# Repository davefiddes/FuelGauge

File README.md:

# Linear Fuel Gauge

This project allows an accurate linear fuel readout to be created for vehicles with unusually shaped fuel tanks and/or mismatched fuel senders.

## Why?

I built this for my Ultima GTR kit car which uses a conventional VDO fuel gauge and vertical float sender unit. The fuel tank on the car is a very unusual shape so it can get as much fuel as possible into a small space. This combination means that with a thirsty V8 the fuel quickly drops from 100% to 25% but takes a lot longer to go from 25% to empty. It's easy to run out of fuel!

To illustrate the scale of the problem here is a rendering of the fuel tank with 15 litres of fuel in a 34 litre tank:

Other Ultima owners have solved the problem by using their ECU or an intelligent dashboard. I have neither and wanted to preserve the original look of the Ultima branded instruments.

## How?

The Linear Fuel Gauge box sits between a standard resistance fuel sender and a hot-wire fuel gauge. The device:

* measures the resistance of the sender (0-100 ohms)
* maps that resistance to a linear fuel level value
* maps the fuel level to a particular gauge output value
* emulates the resistance value needed to achieve the required gauge output value

## Hardware

The gauge is built around a simple 8-pin PIC12F1840 micro-controller. The resistance of the sender is measured using a 10mA current source built from an LM317L regulator. The gauge output is achieved by feeding a PWM signal from the MCU into a high-current MOSFET driver (currents are typically around 100mA for 100%). A simple NPN-transistor driver is provided for low fuel indication. Configuration of the gauge is achieved with a 3-wire TTL serial connection to the MCU.

The project contains the full Kicad schematics and a PCB layout designed to fit in a small Hammond Manufacturing 1591ABK ABS plastic case.

Details:

* [Schematics](hardware/FuelGauge.pdf)
* [PCB Gerbers](hardware/gerbers/FuelGauge-1.0.zip)
* [BOM](docs/BOM.md)
* [Example Wiring Harness](wiring/wiring.pdf)

## Software

The gauge is implemented in C as a platform neutral core with a small hardware abstraction layer for the MCU. A full set of unit tests is provided for the core allowing easy testing and debugging to be carried out on a PC before building for the MCU. The MCU firmware is built using the Microchip MPLAB X IDE v5.15 and xc8 v2.05 compiler (Free Version).

 The gauge has two 9 bin maps that allow fine grained mapping of:

* the input resistance to a linear fuel level
* the linear fuel level to a PWM gauge output value

 The calibration of the two maps is achieved using a serial connection. The core implements a command processor allowing values in each of the maps to be modified and saved to EEPROM. During calibration the gauge output can be tested and the resistance of the fuel sender measured independently.

 The [Calibration And Programming Guide](docs/user-guide.md) details how to set up the fuel gauge which should mostly be a one-time exercise.

## License

 The device hardware and software is covered by the GNU General Public License v3.

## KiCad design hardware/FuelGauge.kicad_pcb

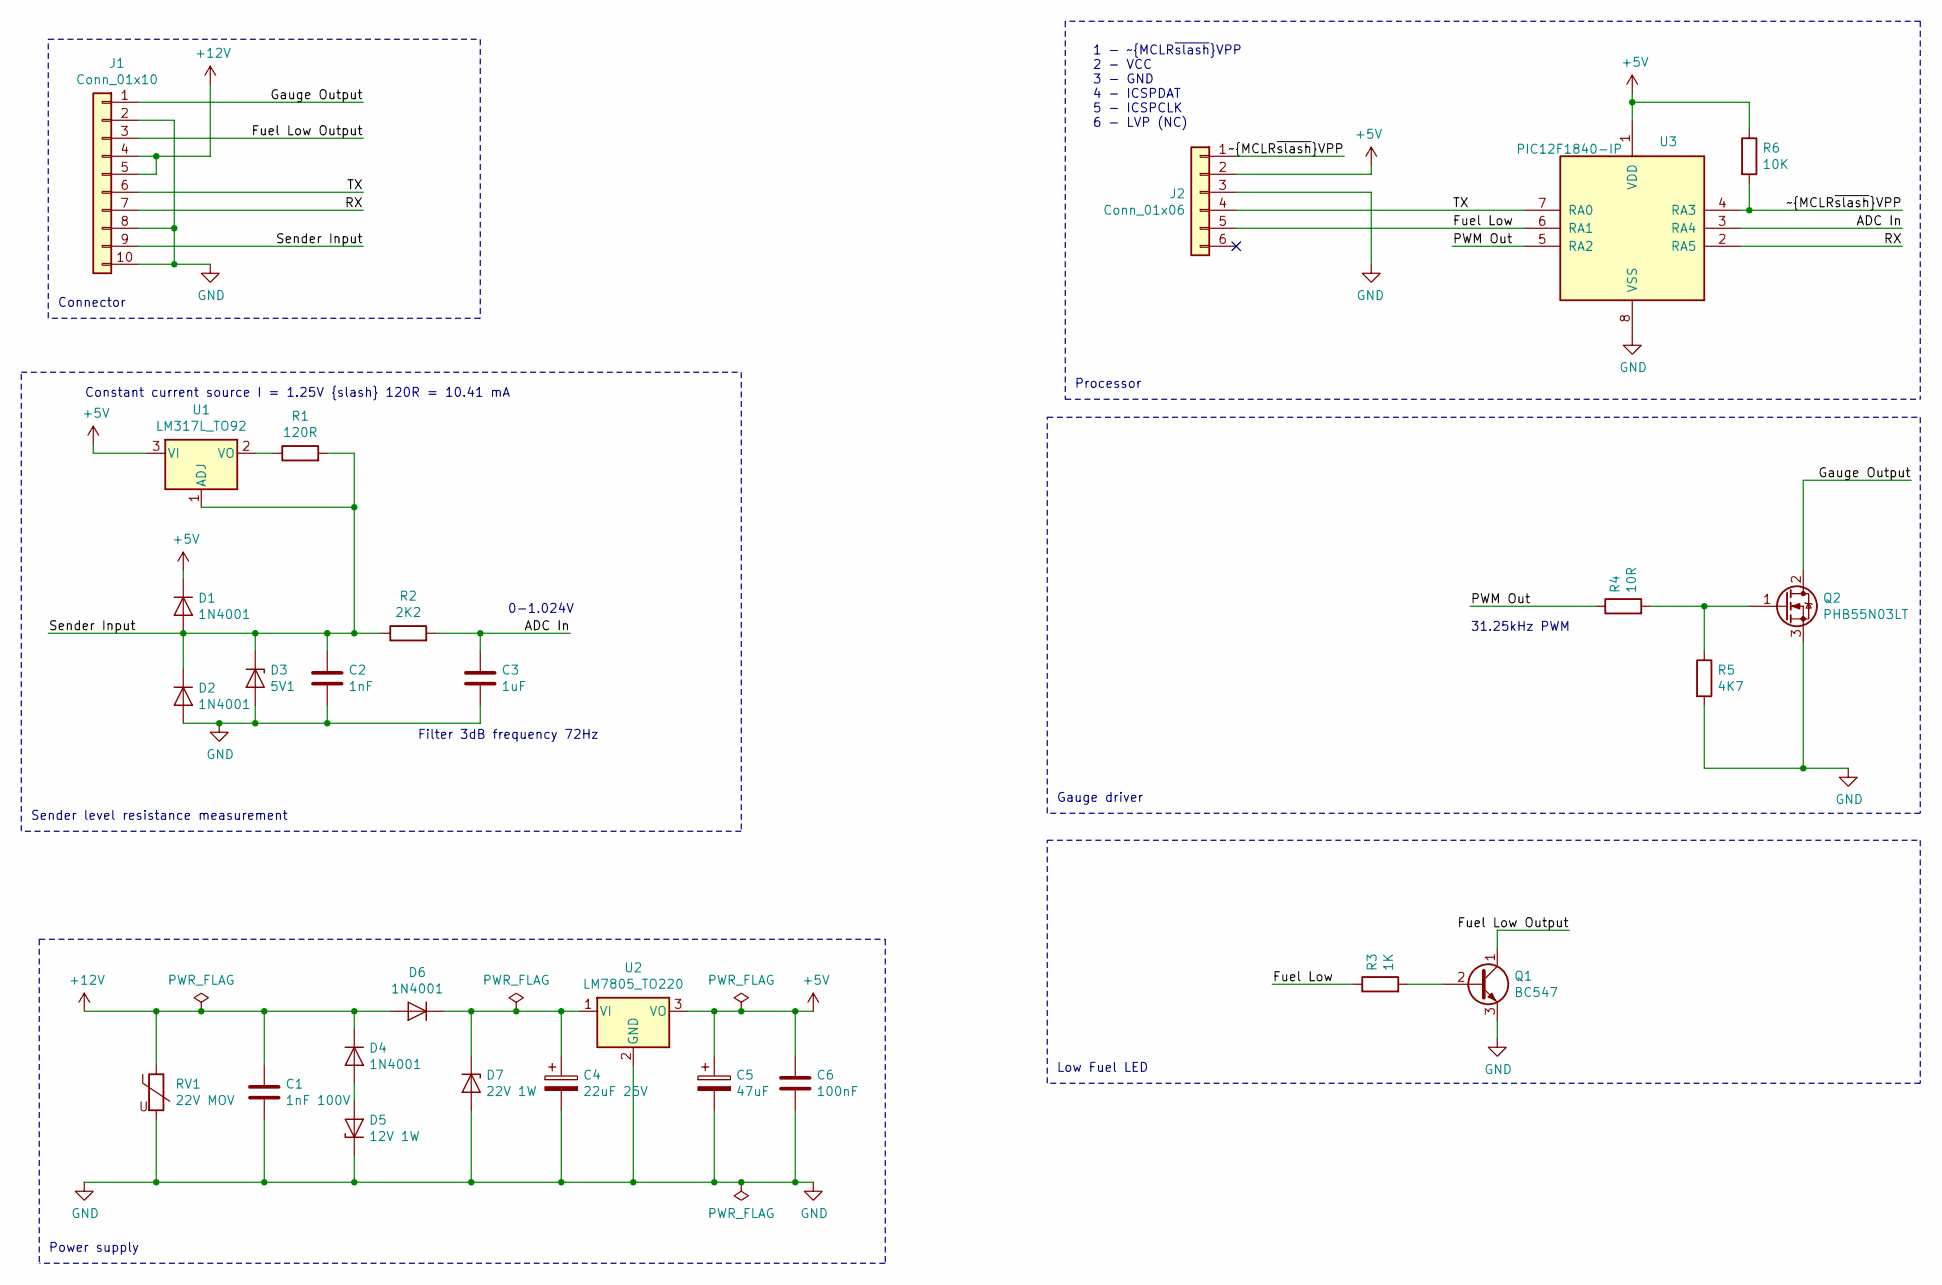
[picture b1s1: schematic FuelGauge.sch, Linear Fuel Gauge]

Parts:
C1: 1nF 100V; C_Rect_L7.0mm_W6.0mm_P5.00mm
C2: 1nF; C_Disc_D3.0mm_W1.6mm_P2.50mm
C3: 1uF; C_Rect_L7.0mm_W6.0mm_P5.00mm
C4: 22uF 25V; CP_Radial_D5.0mm_P2.00mm
C5: 47uF; CP_Radial_Tantal_D6.0mm_P5.00mm
C6: 100nF; C_Disc_D3.4mm_W2.1mm_P2.50mm
D1, D2, D4, D6: 1N4001; D_DO-41_SOD81_P10.16mm_Horizontal
D3: 5V1; D_DO-41_SOD81_P10.16mm_Horizontal
D5: 12V 1W; D_DO-41_SOD81_P10.16mm_Horizontal
D7: 22V 1W; D_DO-41_SOD81_P10.16mm_Horizontal
J1: Conn_01x10; Molex_KK-254_AE-6410-10A_1x10_P2.54mm_Vertical
J2: Conn_01x06; PinHeader_1x06_P2.54mm_Vertical
Q1: BC547; TO-92_Inline
Q2: PHB55N03LT; TO-263-3_TabPin2
R1: 120R; R_Axial_DIN0207_L6.3mm_D2.5mm_P10.16mm_Horizontal
R2: 2K2; R_Axial_DIN0207_L6.3mm_D2.5mm_P10.16mm_Horizontal
R3: 1K; R_Axial_DIN0207_L6.3mm_D2.5mm_P10.16mm_Horizontal
R4: 10R; R_Axial_DIN0207_L6.3mm_D2.5mm_P10.16mm_Horizontal
R5: 4K7; R_Axial_DIN0207_L6.3mm_D2.5mm_P10.16mm_Horizontal
R6: 10K; R_Axial_DIN0207_L6.3mm_D2.5mm_P10.16mm_Horizontal
RV1: 22V MOV; RV_Disc_D7mm_W3.4mm_P5mm
U1: LM317L_TO92; TO-92_Inline
U2: LM7805_TO220; TO-220-3_Horizontal_TabDown
U3: PIC12F1840-IP; DIP-8_W7.62mm

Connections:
+5V: C5.1, C6.1, D1.1 (K), J2.2, R6.1, U1.3 (VI), U2.3 (VO), U3.1 (VDD)
+12V: C1.1, D4.1 (K), D6.2 (A), J1.4, J1.5, RV1.1
/ADC In: C3.1, R2.2, U3.3 (RA4)
/Fuel Low: J2.5, R3.1, U3.6 (RA1)
/Fuel Low Output: J1.3, Q1.1 (C)
/Gauge Output: J1.1, Q2.2 (D)
/PWM Out: R4.1, U3.5 (RA2)
/RX: J1.7, U3.2 (RA5)
/Sender Input: C2.1, D1.2 (A), D2.1 (K), D3.1 (K), J1.9, R1.2, R2.1, U1.1 (ADJ)
/TX: J1.6, J2.4, U3.7 (RA0)
/~MCLR~/VPP: J2.1, R6.2, U3.4 (RA3)
GND: C1.2, C2.2, C3.2, C4.2, C5.2, C6.2, D2.2 (A), D3.2 (A), D5.1 (K), D7.2 (A), J1.2, J1.8, J1.10, J2.3, Q1.3 (E), Q2.3 (S), R5.2, RV1.2, U2.2 (GND), U3.8 (VSS)
unnamed: C4.1, D6.1 (K), D7.1 (K), U2.1 (VI)
unnamed: D4.2 (A), D5.2 (A)
unnamed: Q1.2 (B), R3.2
unnamed: Q2.1 (G), R4.2, R5.1
unnamed: R1.1, U1.2 (VO)

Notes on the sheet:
Constant current source I = 1.25V {slash} 120R = 10.41 mA
Filter 3dB frequency 72Hz
0-1.024V
31.25kHz PWM
Connector
Sender level resistance measurement
Processor
Gauge driver
Low Fuel LED
Power supply
1 - ~MCLR~{slash}VPP 2 - VCC 3 - GND 4 - ICSPDAT 5 - ICSPCLK 6 - LVP (NC)

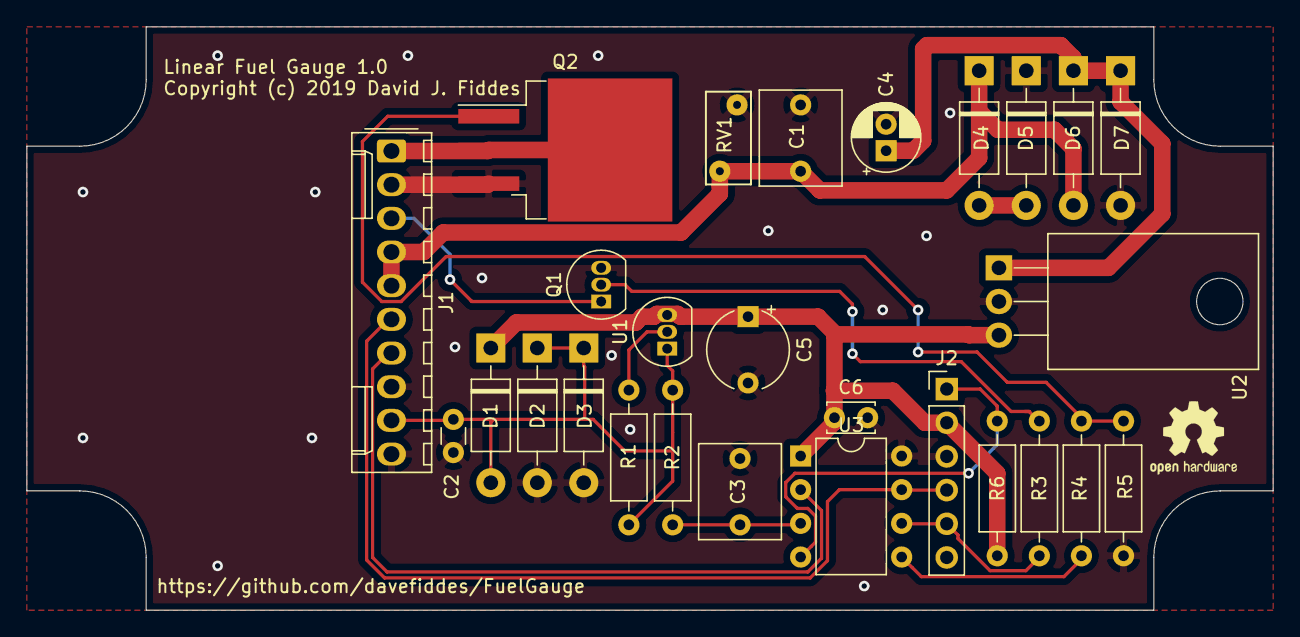
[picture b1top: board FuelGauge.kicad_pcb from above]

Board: 2 copper layers, 94.0 x 44.0 mm, 28 parts (0 on the bottom side), 17 nets.

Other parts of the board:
Logo1: OSHW-Logo2_7.3x6mm_SilkScreen

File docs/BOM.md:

Fuel Gauge Bill of Materials
--------------------------------

Below is the Bill of Materials for the Fuel Gauge 1.0 board:

```
Ref(s)      Value                                   RS Components P/N
-------------------------------------------------------------------------------
C1,C2       1nF 100Vdc Multi-layer Ceramic 10%          699-5109
C3          1uF 100Vdc Polyester 10%                    126-2282
C4          22uF Aluminium Electrolytic 35Vdc           715-2729
C5          47uF 6.3V Radial Tantalum                   868-5690
C6          100nF 50Vdc Multi-layer Ceramic 10%         538-1310
D1,D2,D4,D6 1N4001                                      628-8931
D3          5V1 1W Zener Diode                          166-2747
D5          12V 1W Zener Diode                          687-5459
D7          22V 1.3W Zener Diode                        813-3915
J1          Molex KK 254 7395, 2.54mm Pitch, 10 Way     173-2994
            1 Row, Right Angle PCB Header
J2          6 Way 1 Row 2.54mm Pitch header
Q1          BC547 NPN Transistor TO-92                  671-1113
Q2          PHB55N03LT N-MOSFET transistor TO-263
R1          120R 1/4W 1% thin-film resistor
R2          2K2 1/4W 1% thin-film resistor
R3          1K 1/4W 1% thin-film resistor
R4          10R 1/4W 1% thin-film resistor
R5          4K7 1/4W 1% thin-film resistor
R6          10K 1/4W 1% thin-film resistor
RV1         Panasonic ERZV05D220 22V MOV                226-7817
U1          LM317L 100mA Linear regulator TO92          661-6796
U2          LM7805 700mA Linear Regulator TO220         785-6762
U3          Microchip PIC12F1840-I/P DIP-8              743-2697
```

Notes:
 * Q2 may be hard to find. Any power N-channel MOSFET in TO-263 package should suffice. I used a device recovered from a PC motherboard as that what I had available.

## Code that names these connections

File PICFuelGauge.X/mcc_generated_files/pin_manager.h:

/**
  @Generated Pin Manager Header File

  @Company:
    Microchip Technology Inc.

  @File Name:
    pin_manager.h

  @Summary:
    This is the Pin Manager file generated using PIC10 / PIC12 / PIC16 / PIC18 MCUs

  @Description
    This header file provides APIs for driver for .
    Generation Information :
        Product Revision  :  PIC10 / PIC12 / PIC16 / PIC18 MCUs - 1.76
        Device            :  PIC12F1840
        Driver Version    :  2.11
    The generated drivers are tested against the following:
        Compiler          :  XC8 2.00
        MPLAB 	          :  MPLAB X 5.10	
*/

/*
    (c) 2018 Microchip Technology Inc. and its subsidiaries. 
    
    Subject to your compliance with these terms, you may use Microchip software and any 
    derivatives exclusively with Microchip products. It is your responsibility to comply with third party 
    license terms applicable to your use of third party software (including open source software) that 
    may accompany Microchip software.
    
    THIS SOFTWARE IS SUPPLIED BY MICROCHIP "AS IS". NO WARRANTIES, WHETHER 
    EXPRESS, IMPLIED OR STATUTORY, APPLY TO THIS SOFTWARE, INCLUDING ANY 
    IMPLIED WARRANTIES OF NON-INFRINGEMENT, MERCHANTABILITY, AND FITNESS 
    FOR A PARTICULAR PURPOSE.
    
    IN NO EVENT WILL MICROCHIP BE LIABLE FOR ANY INDIRECT, SPECIAL, PUNITIVE, 
    INCIDENTAL OR CONSEQUENTIAL LOSS, DAMAGE, COST OR EXPENSE OF ANY KIND 
    WHATSOEVER RELATED TO THE SOFTWARE, HOWEVER CAUSED, EVEN IF MICROCHIP 
    HAS BEEN ADVISED OF THE POSSIBILITY OR THE DAMAGES ARE FORESEEABLE. TO 
    THE FULLEST EXTENT ALLOWED BY LAW, MICROCHIP'S TOTAL LIABILITY ON ALL 
    CLAIMS IN ANY WAY RELATED TO THIS SOFTWARE WILL NOT EXCEED THE AMOUNT 
    OF FEES, IF ANY, THAT YOU HAVE PAID DIRECTLY TO MICROCHIP FOR THIS 
    SOFTWARE.
*/

#ifndef PIN_MANAGER_H
#define PIN_MANAGER_H

/**
  Section: Included Files
*/

#include <xc.h>

#define INPUT   1
#define OUTPUT  0

#define HIGH    1
#define LOW     0

#define ANALOG      1
#define DIGITAL     0

#define PULL_UP_ENABLED      1
#define PULL_UP_DISABLED     0

// get/set RA0 procedures
#define RA0_SetHigh()            do { LATAbits.LATA0 = 1; } while(0)
#define RA0_SetLow()             do { LATAbits.LATA0 = 0; } while(0)
#define RA0_Toggle()             do { LATAbits.LATA0 = ~LATAbits.LATA0; } while(0)
#define RA0_GetValue()              PORTAbits.RA0
#define RA0_SetDigitalInput()    do { TRISAbits.TRISA0 = 1; } while(0)
#define RA0_SetDigitalOutput()   do { TRISAbits.TRISA0 = 0; } while(0)
#define RA0_SetPullup()             do { WPUAbits.WPUA0 = 1; } while(0)
#define RA0_ResetPullup()           do { WPUAbits.WPUA0 = 0; } while(0)
#define RA0_SetAnalogMode()         do { ANSELAbits.ANSA0 = 1; } while(0)
#define RA0_SetDigitalMode()        do { ANSELAbits.ANSA0 = 0; } while(0)

// get/set lowFuel aliases
#define lowFuel_TRIS                 TRISAbits.TRISA1
#define lowFuel_LAT                  LATAbits.LATA1
#define lowFuel_PORT                 PORTAbits.RA1
#define lowFuel_WPU                  WPUAbits.WPUA1
#define lowFuel_ANS                  ANSELAbits.ANSA1
#define lowFuel_SetHigh()            do { LATAbits.LATA1 = 1; } while(0)
#define lowFuel_SetLow()             do { LATAbits.LATA1 = 0; } while(0)
#define lowFuel_Toggle()             do { LATAbits.LATA1 = ~LATAbits.LATA1; } while(0)
#define lowFuel_GetValue()           PORTAbits.RA1
#define lowFuel_SetDigitalInput()    do { TRISAbits.TRISA1 = 1; } while(0)
#define lowFuel_SetDigitalOutput()   do { TRISAbits.TRISA1 = 0; } while(0)
#define lowFuel_SetPullup()          do { WPUAbits.WPUA1 = 1; } while(0)
#define lowFuel_ResetPullup()        do { WPUAbits.WPUA1 = 0; } while(0)
#define lowFuel_SetAnalogMode()      do { ANSELAbits.ANSA1 = 1; } while(0)
#define lowFuel_SetDigitalMode()     do { ANSELAbits.ANSA1 = 0; } while(0)

// get/set RA2 procedures
#define RA2_SetHigh()            do { LATAbits.LATA2 = 1; } while(0)
#define RA2_SetLow()             do { LATAbits.LATA2 = 0; } while(0)
#define RA2_Toggle()             do { LATAbits.LATA2 = ~LATAbits.LATA2; } while(0)
#define RA2_GetValue()              PORTAbits.RA2
#define RA2_SetDigitalInput()    do { TRISAbits.TRISA2 = 1; } while(0)
#define RA2_SetDigitalOutput()   do { TRISAbits.TRISA2 = 0; } while(0)
#define RA2_SetPullup()             do { WPUAbits.WPUA2 = 1; } while(0)
#define RA2_ResetPullup()           do { WPUAbits.WPUA2 = 0; } while(0)
#define RA2_SetAnalogMode()         do { ANSELAbits.ANSA2 = 1; } while(0)
#define RA2_SetDigitalMode()        do { ANSELAbits.ANSA2 = 0; } while(0)

// get/set tank aliases
#define tank_TRIS                 TRISAbits.TRISA4
#define tank_LAT                  LATAbits.LATA4
#define tank_PORT                 PORTAbits.RA4
#define tank_WPU                  WPUAbits.WPUA4
#define tank_ANS                  ANSELAbits.ANSA4
#define tank_SetHigh()            do { LATAbits.LATA4 = 1; } while(0)
#define tank_SetLow()             do { LATAbits.LATA4 = 0; } while(0)
#define tank_Toggle()             do { LATAbits.LATA4 = ~LATAbits.LATA4; } while(0)
#define tank_GetValue()           PORTAbits.RA4
#define tank_SetDigitalInput()    do { TRISAbits.TRISA4 = 1; } while(0)
#define tank_SetDigitalOutput()   do { TRISAbits.TRISA4 = 0; } while(0)
#define tank_SetPullup()          do { WPUAbits.WPUA4 = 1; } while(0)
#define tank_ResetPullup()        do { WPUAbits.WPUA4 = 0; } while(0)
#define tank_SetAnalogMode()      do { ANSELAbits.ANSA4 = 1; } while(0)
#define tank_SetDigitalMode()     do { ANSELAbits.ANSA4 = 0; } while(0)

// get/set RA5 procedures
#define RA5_SetHigh()            do { LATAbits.LATA5 = 1; } while(0)
#define RA5_SetLow()             do { LATAbits.LATA5 = 0; } while(0)
#define RA5_Toggle()             do { LATAbits.LATA5 = ~LATAbits.LATA5; } while(0)
#define RA5_GetValue()              PORTAbits.RA5
#define RA5_SetDigitalInput()    do { TRISAbits.TRISA5 = 1; } while(0)
#define RA5_SetDigitalOutput()   do { TRISAbits.TRISA5 = 0; } while(0)
#define RA5_SetPullup()             do { WPUAbits.WPUA5 = 1; } while(0)
#define RA5_ResetPullup()           do { WPUAbits.WPUA5 = 0; } while(0)

/**
   @Param
    none
   @Returns
    none
   @Description
    GPIO and peripheral I/O initialization
   @Example
    PIN_MANAGER_Initialize();
 */
void PIN_MANAGER_Initialize (void);

/**
 * @Param
    none
 * @Returns
    none
 * @Description
    Interrupt on Change Handling routine
 * @Example
    PIN_MANAGER_IOC();
 */
void PIN_MANAGER_IOC(void);



#endif // PIN_MANAGER_H
/**
 End of File
*/

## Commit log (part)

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2019-04-11 Initial commit of a FuleGauge mapping function
    This initial commit contains an interpolating mapping funtion that
    allows a 16-bit value to be mapped to another numebr space. It
    uses a 9 bin map with linear interploation between bins.
    A unit test is provided.
2019-04-11 Add a simple Linux command line demo program
    This should allow the Fuel Gauge functionality to be tested and
    debugged on a PC.
2019-05-03 Initial command processor, bare bones HAL and tests
    This is an initial fuel gauge command processor. It is capable of
    reading tank input values, setting gauge output values and switching
    between run and program modes.
    A bare bones HAL is defined and test implementation provided to
    verify correct operation.
    Tests:
2019-05-03 Implement loading of maps
    This refactors the test functions used to load input and output maps
    to use HAL functions and the "l" load command.
    Global variables within the command processor are now static to
    limit their scope as they did not need to be global.
    Tests:
    - Run all unit tests successfully
2019-05-04 Display input and output maps
    This implements the ability to display the input and output maps
    on the console allowing the configuration to be saved externally
    and debugged.
    Tests:
    - Run updated unit tests.
2019-05-04 Change input and output maps to use the correct naming
    This changes the naming convention for the static module variables
    containing our input and output maps to follow the expected
    convetion. g_ is reserved for truly global variables which these are
    not.
    Tests:
    - Rebuild and run existing unit tests
2019-05-04 Implement normal gauge operation
    This implements normal guage operation by providing a function
    which can be called from a main loop. This then carries out the
    same process as a one-shot mapping but without any logging of
    the input, actual tank level and output values.
    Tests:
    - Run the updated units tests
2019-05-05 Remove printf dependency
    Remove the printf dependency by adding a simpler print text and
    newline HAL. Two simple routines are added to format uint16_t
    values and bin numbers. The buffers for these are added on the
    stack which may require changing to be static depending on how
    XC8 reacts.
    The newlines in the test case have been removed as these are
2019-05-05 Add an initialisation function allowing the gauge to start up cleanly
    This adds an initialisation funciton which causes the HAL to load
    into the gauge.
    The public functions in the module are reordered cosmetically to
    be clearer
    Tests:
    - Run updated unit tests
2019-05-06 Fix a problem where we output to the gauge when not running
    This addresses a problem where the gauge output would change
    when RunGauge() was called from the main loop but the gauge
    was not in Run mode.
    Tests:
    - Run updated unit tests
2019-05-06 Initial PIC Fuel Guage integration
    This integrates the library with the core application logic with a
    simple HAL for a PIC12F1840 MCU. The main loop uses polling to
    sample the serial port for key presses and build up a command
    buffer which is then sent to the application logic when carriage-
    return is pressed.
    Tests
2019-05-06 Refactor Map Load and Save to remove failure path
    The ability to failure when saving or loading maps just seems to add
    complication. The EEPROM operations don't seem to be easy to
    detect failure. This change removes this from the HAL as a
    simplification.
    Tests:
    - Run updated unit tests
2019-05-06 Simplify empty command processing
    This removes the need for using strlen() when processing
    commands. As with other functions it assumes that a non-NULL
    string pointer is always passed for processing.
    Tests:
    - Run unit tests
2019-05-06 Display usage on start up and on request
    To save from future confusion the device now displays usage
    information on start up and on request with the "u" command.
    Tests:
    - Verify output on startup and on issuing the "u" command
    - Run updated (noddy) unit test
2019-05-09 Change the ADC reference to be 1.024V
    This changes the ADC voltage reference to use the FVR rather
    than the VDD supply rail. Using this voltage reference for the ADC
    allows it to produce accurate readings when hooked up to the
    resistance sensing hardware rather than a 100k ohm pot
    connected between the supply rails.
    Tests:
2019-05-11 Feature complete HW design with hack PCB layout
    This completes the HW after testing on a breadboard. Both the
    sender input and gauge output have been tested.
    A fuel low output has been hacked together though this has no
    software currently and may be replaced with a 12V indicator.
    The PCB layout is functional and passes DRC but is pretty awful
    otherwise.
2019-05-16 Version 1.0 hardware
    This change contains what is hoped to be 1.0 hardware. It removes the complex MOSFET driver for a simple direct drive
    from the MCU. The LED has been removed as this appears to
    provide little value as the VDO test guage uses 65% to 98% duty
    cycle to cover 0% to 100% which is virtually imperceptible.
    A simple transistor driver for a low fuel warning LED or lamp has
    been included. This should work with a 12V LED indicator lamp.
2019-05-16 Manufacturing files submitted for 1.0 hardware
    This updates the PDF with the final schematic. It also updates the
    PCB to include the back solder mask which was missing. The
    gerbers areplotted from this, zipped and included in the source tree.
    The Kicad cache files which don't need to be version tracked are
    excluded from git.
    Tests:
2019-05-17 Revert "Add a simple Linux command line demo program"
    This reverts commit dc7700577bad489c318369ecf33b33b0526fba76.
2019-05-21 Include googletest as a gi submodule locally
    This includes googletest as a git submodule as described here:
    https://david-grs.github.io/cpp-clang-travis-cmake-gtest-coveralls-appveyor/
    Doing this removes a system dependency on googletest packages
    and will allow for Travis CI integration in the future.
    Tests:
    - Fully reconfigure and rebuild the project
2019-05-21 Fix gtest submodule to allow anonymous cloning
    This fixes the gtest git submodule to use the HTTPS URL for
    googletest which can be cloned anonymously. The Travis-CI build
    failed because it was trying to use SSH which is what I use locally
    and was picked up by git when the submodule was added.
    Tests:
    - Remove gtest subdirectory and run git submodule update
2019-05-21 Fix cmake build path
    On Travis-CI the build fails with:
    $ cmake --build ..
    Error: could not load cache
    This is because the path for the --build command should be . (i.e.
    the build directory) rather than .. (the source directory).
    Tests:
2019-05-21 Update pthread link order
    This fixes an ordering issue when linking with pthread by using the
    mechanism defined in CMake 3.1 to configure the link order for the pthreads library found on the system. This allows the code to build on Fedora 30 (where link order isn't as fussy) and Ubuntu Xenial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
    Tests:
    - Clean build and test run on Fedora 30
    - Clean build and test run on Ubuntu Xenial Docker container
2019-05-24 Implement a Low Fuel Warning Light
    This change implements a low fuel warning light. The light is
    attached to pin6 of the MCU and is activated by pulling this GPIO
    pin low.
    A low fuel level setting is maintained in EEPROM alongside the
    input and output maps. It is configured using the new "f"
    command which is similar to the existing "g" gauge output
2019-05-28 Generate a version number from the current git commit
    This generates a version number for the firmware from the
    current git commit. Based on a recipe from:
    https://www.microchip.com/forums/m995841.aspx
    The usage print out on start-up has been removed which
    speeds start up significantly.
    Tests:
2019-05-28 Indicate an error with the tank input being out of range
    This checks the tank input ADC to see if it is going full scale.
    This indicates that there is an error with the sender
    resistance sensing. The error is indicated to the user by
    flashing the low fuel indicator.
    Slightly odd side-effect is that in continuous mode the sensor
    logging output stops while there is an error. Outputting text
2019-05-28 Fix TankInputValidation unit test error
    Having tried to log the input error in continuous mode this
    broke the flashing (by delaying for too long). The unit test was not updated to remove the expectation of the new error.
    This change fixes that.
    Tests:
    - Run updated unit tests successfully.
2019-05-30 Fix a sensor error not being reported on startup
    This fixes an issue found where the board starts up without a
    sensor connected but the low fuel LED would not flash to
    indicate the error condition. Upon inspection it appears that
    the errorCount is not being initialised. This causes the
    errorCode value to contain random values which can take a
    long time in the error condition before it starts flashing.
2019-07-07 Replace the over-optimised implementation of MapValue()
    This replaces the over-optimised implementation of
    MapValue() which makes a static assumption that the top 3
    bits can be used to identify the output map bin by one which
    uses an explicit input map. This is much more accurate.
    Update all the tests across the system to remove the fudging
    required because the top value cannot fit 0x10000 in a
2019-07-08 Print the full map for input and output
    Now that a more flexible scheme has been adopted for
    mapping between the tank input, actual fuel level and gauge
    output display the full details of the input and output maps.
    Update the expected text output for the tests.
    Test:
    - Run updated tests
2019-07-09 Filter the tank input to remove frequencies above 0.62Hz or so
    This applies a simple Exponential Moving Average filter from:
    https://tttapa.github.io/Pages/Mathematics/Systems-and-Control-Theory/Digital-filters/Exponential%20Moving%20Average/C++Implementation.html
    This filters values above about 0.62Hz which combines with
    the hardware filter reducing signals above 72Hz and a 1kHz
    sample rate to provide a smooth output in noisy envirnment.
    Tests:
2019-07-09 Update fuel tank model POV
    Actually save the FreeCAD model of the fuel tank with the POV
    used in the documentation.
2019-07-11 Fix numerical precision issues when running on a 8-bit PIC
    This fixes a problem when running on an 8-bit PIC where the calcuations used in interplotation are not carried out using a 32-bit signed integer as required but as a 16-bit unsigned value. Explicitly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
    Tests:
    - Run updated unit test with a real-world test value
    - Build and run on a PIC and verify in the debugger that the
    calculation is operating the same as the unit test for the
    same input value
2019-07-12 Fix Windows build using MPLABX
    This fixes the Windows build of the project using MPLABX v5.15 by:
    - Adding proper stringification of the GIT_VERSION which
    seems to be required with the Windows version of the xc8
    compiler
    - Remove generated files from the MPLABX/NetBeans
    project. These are quite different between the Windows
2019-07-12 Properly escape the git version string
    This fixes an error in the stringify macro used to include the
    git version that resulted in the string GIT_VERSION being
    displayed rather than the actual hash.
    The quoting in the define passed to the compiler has been
    removed as this caused differences between the Linux and
    Windows builds.
2019-07-28 Add more detailed hardware documentation and BOM
    This updates the hardware doucmentation to include a
    picture of the finished unit. It also adds a detailed BOM with
    RS Components part numbers. Links are provided in the
    Hardware section of the README to point to the schematics
    and PCB gerbers.
    Tests:

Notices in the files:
hardware/FuelGauge.kicad_pcb:
Copyright (c) 2019 David J. Fiddes
